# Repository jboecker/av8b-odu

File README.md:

# ODU panel for the DCS AV8BNA Harrier

This repository contains my first design for the ODU panel of the Harrier to use with DCS-BIOS.
It does not use accurate dimensions.

The Arduino sketch uses my modified version of the LedDisplay library:
https://github.com/jboecker/LedDisplay

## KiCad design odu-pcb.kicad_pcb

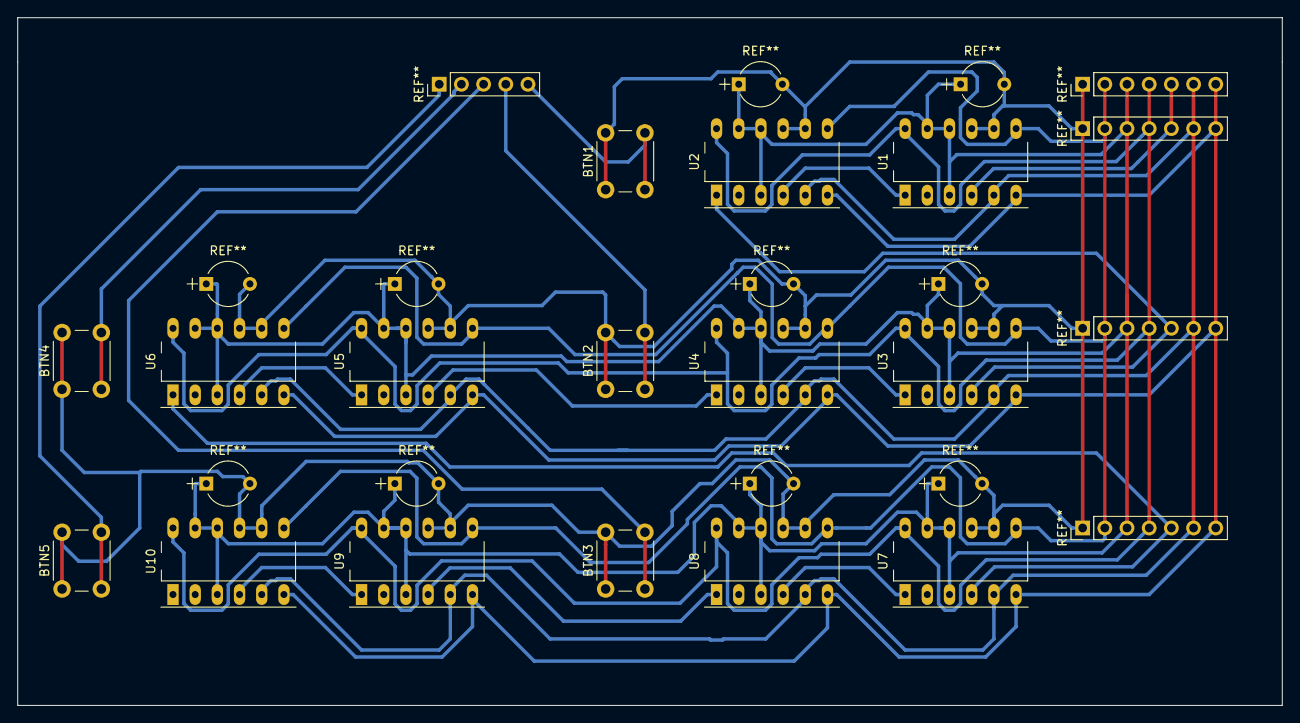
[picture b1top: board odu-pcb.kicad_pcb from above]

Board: 2 copper layers, 144.8 x 78.7 mm, 15 parts (0 on the bottom side), 15 nets.

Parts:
BTN1, BTN2, BTN3, BTN4, BTN5: SW_Push; SW_PUSH_6mm_h4.3mm
U1, U2, U3, U4, U5, U6, U7, U8, U9, U10: HCMS; HCMS_DIP-12_W7.62mm_Socket_LongPads

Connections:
CE: U1.7, U2.7, U3.7, U4.7, U5.7, U6.7, U7.7, U8.7, U9.7, U10.7
CLK: U1.6, U2.6, U3.6, U4.6, U5.6, U6.6, U7.6, U8.6, U9.6, U10.6
DOUTU1_TO_DINU2: U1.1, U2.4
DOUTU2_TO_DINU3: U2.1, U3.4
DOUTU3_TO_DINU4: U3.1, U4.4
DOUTU4_TO_DINU5: U4.1, U5.4
DOUTU5_TO_DINU6: U5.1, U6.4
DOUTU6_TO_DINU7: U6.1, U7.4
DOUTU7_TO_DINU8: U7.1, U8.4
DOUTU8_TO_DINU9: U8.1, U9.4
DOUTU9_TO_DINU10: U9.1, U10.4
GND: BTN1.1, BTN2.1, BTN3.1, BTN4.1, BTN5.1, U1.8, U1.9, U2.8, U2.9, U3.8, U3.9, U4.8, U4.9, U5.8, U5.9, U6.8, U6.9, U7.8, U7.9, U8.8, U8.9, U9.8, U9.9, U10.8, U10.9
RESET: U1.12, U2.12, U3.12, U4.12, U5.12, U6.12, U7.12, U8.12, U9.12, U10.12
RS: U1.5, U2.5, U3.5, U4.5, U5.5, U6.5, U7.5, U8.5, U9.5, U10.5
VCC: U1.3, U1.10, U1.11, U2.3, U2.10, U2.11, U3.3, U3.10, U3.11, U4.3, U4.10, U4.11, U5.3, U5.10, U5.11, U6.3, U6.10, U6.11, U7.3, U7.10, U7.11, U8.3, U8.10, U8.11, U9.3, U9.10, U9.11, U10.3, U10.10, U10.11

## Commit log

2019-09-17 initial commit and first prototype
2019-09-17 Revision 2: Buttons, no airwires (uses stripboard with two trace cuts as back side
2019-11-15 add netlist, pcb2gcode parameters and enclosure design
2019-11-15 Add Arduino sketch and README.md
